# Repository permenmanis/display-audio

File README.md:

# display-audio
develop display audio
silahkan digunakan dengan baik, belajar bersama untuk lebih baik

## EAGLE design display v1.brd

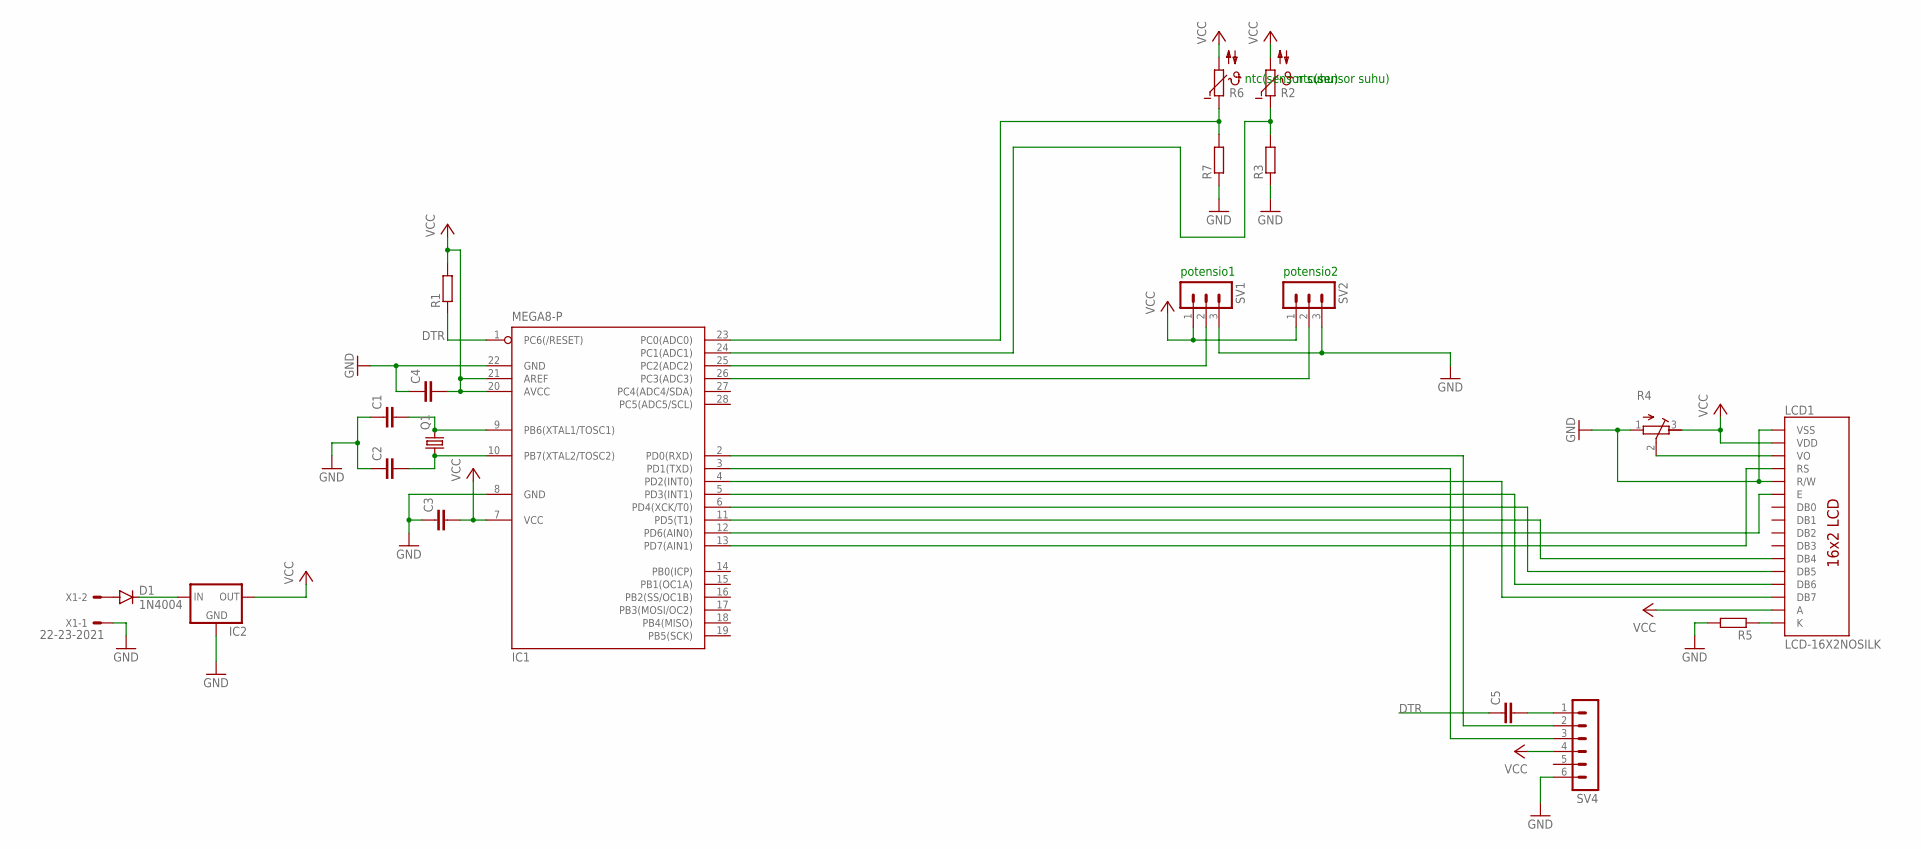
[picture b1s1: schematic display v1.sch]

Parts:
C1, C2: C-EU025-025X050; C025-025X050
C3, C4, C5: C-EU050-025X075; C050-025X075
D1: 1N4004; DO41-10
IC1: MEGA8-P; DIL28-3
IC2: 78XXL
LCD1: LCD-16X2NOSILK; LCD-16X2_NOSILK
Q1: CRYSTALHC49S; HC49/S
R1, R3, R5, R7: R-EU_0204/7; 0204/7
R2, R6: NTC642-6; P642
R4: R-TRIMM64W; RTRIM64W
SV1, SV2: MA03-1
SV4: MA06-1
X1: 22-23-2021

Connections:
DTR: C5.1, IC1.1 (PC6(/RESET)), R1.1
GND: C1.1, C2.1, C3.1, C4.1, IC1.8 (GND), IC1.22 (GND), IC2.GND, LCD1.1 (VSS), LCD1.5 (R/W), R3.1, R4.1 (A), R5.2, R7.1, SV1.3, SV2.3, SV4.6, X1.1
unnamed: C1.2, IC1.9 (PB6(XTAL1/TOSC1)), Q1.2
unnamed: IC1.12 (PD6(AIN0)), LCD1.6 (E)
unnamed: C2.2, IC1.10 (PB7(XTAL2/TOSC2)), Q1.1
unnamed: IC1.13 (PD7(AIN1)), LCD1.4 (RS)
unnamed: IC1.23 (PC0(ADC0)), R6.1, R7.2
unnamed: D1.C, IC2.IN
unnamed: IC1.24 (PC1(ADC1)), R2.1, R3.2
unnamed: IC1.4 (PD2(INT0)), LCD1.14 (DB7)
unnamed: IC1.5 (PD3(INT1)), LCD1.13 (DB6)
unnamed: LCD1.3 (VO), R4.2 (S)
unnamed: IC1.6 (PD4(XCK/T0)), LCD1.12 (DB5)
unnamed: IC1.11 (PD5(T1)), LCD1.11 (DB4)
unnamed: LCD1.16 (K), R5.1
unnamed: C5.2, SV4.1
unnamed: IC1.2 (PD0(RXD)), SV4.2
unnamed: IC1.3 (PD1(TXD)), SV4.3
unnamed: D1.A, X1.2
unnamed: IC1.25 (PC2(ADC2)), SV1.2
unnamed: IC1.26 (PC3(ADC3)), SV2.2
VCC: C3.2, C4.2, IC1.7 (VCC), IC1.20 (AVCC), IC1.21 (AREF), IC2.OUT, LCD1.2 (VDD), LCD1.15 (A), R1.2, R2.2, R4.3 (E), R6.2, SV1.1, SV2.1, SV4.4

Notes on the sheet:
ntc(sensor suhu)
potensio1
potensio2

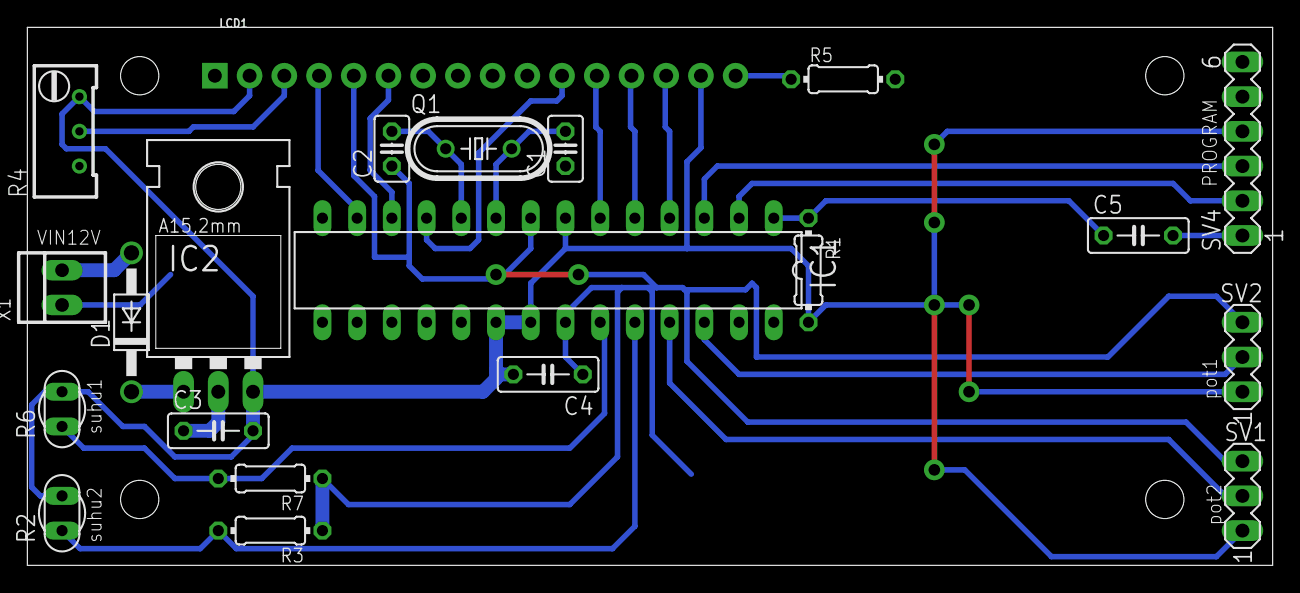
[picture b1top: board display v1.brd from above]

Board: 2 copper layers, 91.1 x 39.4 mm, 21 parts (0 on the bottom side), 22 nets.

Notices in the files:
parts and their libraries:
SparkFun-Displays: Licensing: Creative Commons ShareAlike 4.0 International - https://creativecommons.org/licenses/by-sa/4.0
